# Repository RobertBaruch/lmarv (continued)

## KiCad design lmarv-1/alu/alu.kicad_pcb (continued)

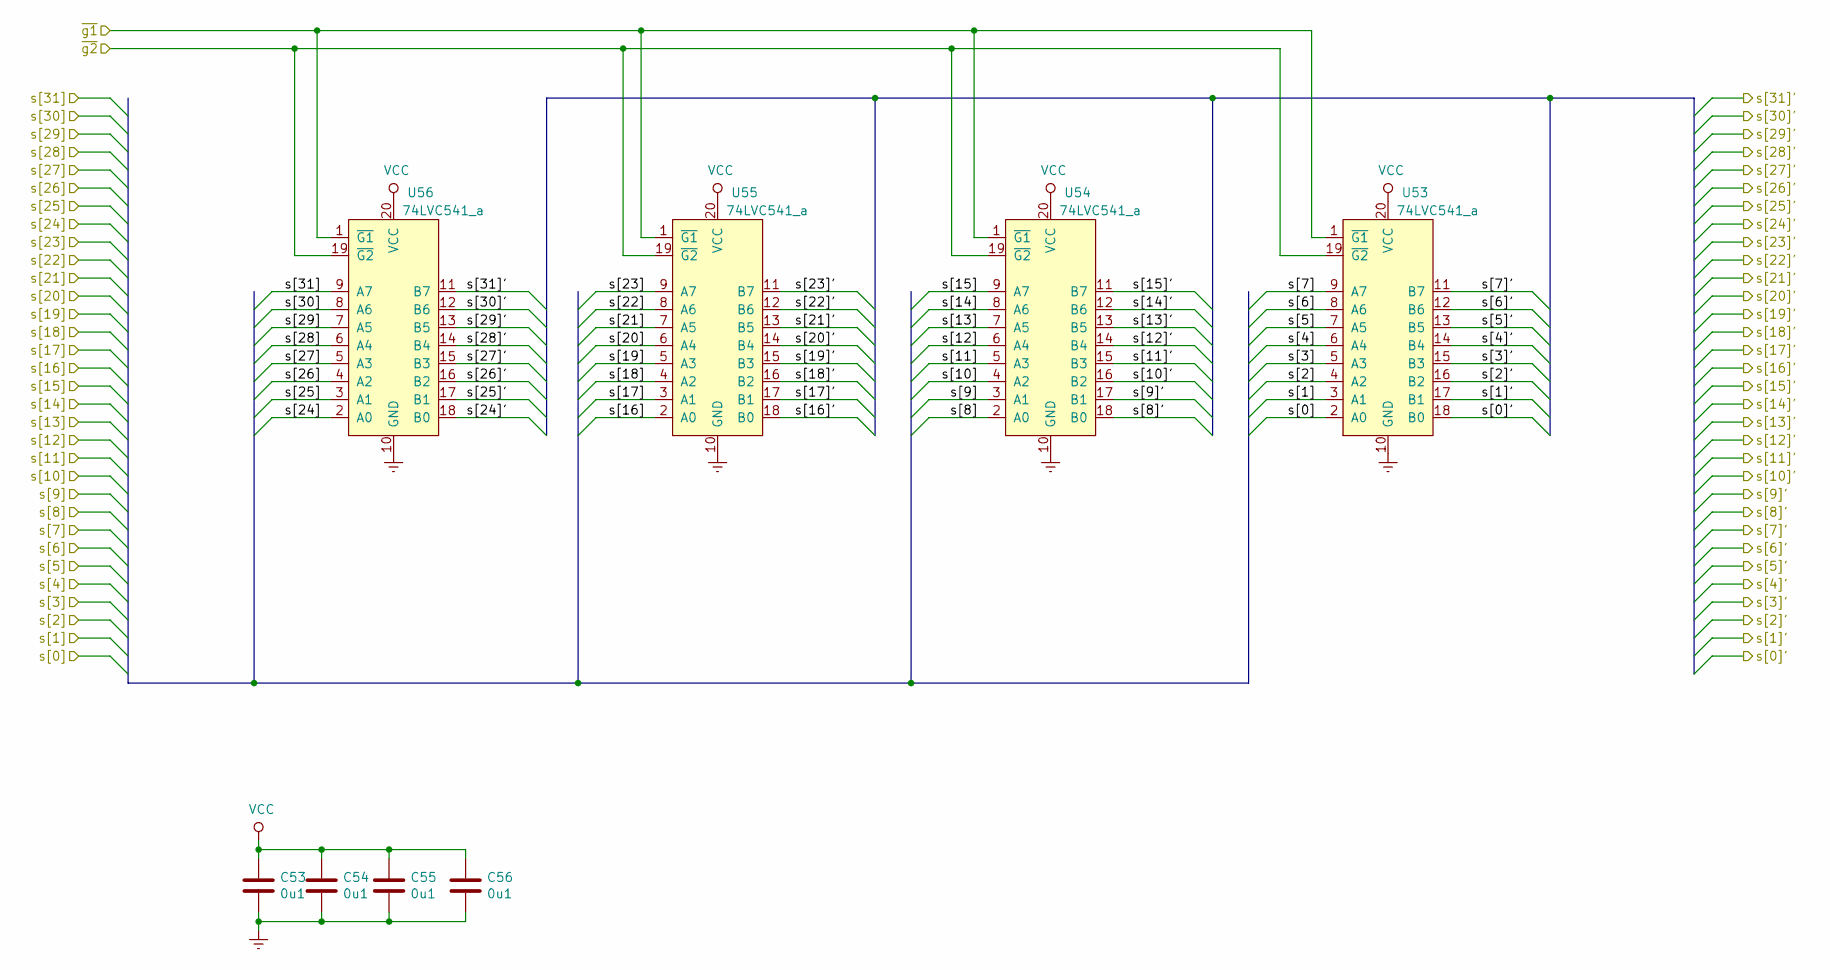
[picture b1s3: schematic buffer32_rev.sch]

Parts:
C13, C14, C15, C16: 0u1; C_0603_1608Metric
U53, U54, U55, U56: 74LVC541_a; TSSOP-20_4.4x6.5mm_P0.65mm

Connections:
/rd[0]: U53.18 (B0); also elsewhere on the board
/rd[1]: U53.17 (B1); also elsewhere on the board
/rd[2]: U53.16 (B2); also elsewhere on the board
/rd[3]: U53.15 (B3); also elsewhere on the board
/rd[4]: U53.14 (B4); also elsewhere on the board
/rd[5]: U53.13 (B5); also elsewhere on the board
/rd[6]: U53.12 (B6); also elsewhere on the board
/rd[7]: U53.11 (B7); also elsewhere on the board
/rd[8]: U54.18 (B0); also elsewhere on the board
/rd[9]: U54.17 (B1); also elsewhere on the board
/rd[10]: U54.16 (B2); also elsewhere on the board
/rd[11]: U54.15 (B3); also elsewhere on the board
/rd[12]: U54.14 (B4); also elsewhere on the board
/rd[13]: U54.13 (B5); also elsewhere on the board
/rd[14]: U54.12 (B6); also elsewhere on the board
/rd[15]: U54.11 (B7); also elsewhere on the board
/rd[16]: U55.18 (B0); also elsewhere on the board
/rd[17]: U55.17 (B1); also elsewhere on the board
/rd[18]: U55.16 (B2); also elsewhere on the board
/rd[19]: U55.15 (B3); also elsewhere on the board
/rd[20]: U55.14 (B4); also elsewhere on the board
/rd[21]: U55.13 (B5); also elsewhere on the board
/rd[22]: U55.12 (B6); also elsewhere on the board
/rd[23]: U55.11 (B7); also elsewhere on the board
/rd[24]: U56.18 (B0); also elsewhere on the board
/rd[25]: U56.17 (B1); also elsewhere on the board
/rd[26]: U56.16 (B2); also elsewhere on the board
/rd[27]: U56.15 (B3); also elsewhere on the board
/rd[28]: U56.14 (B4); also elsewhere on the board
/rd[29]: U56.13 (B5); also elsewhere on the board
/rd[30]: U56.12 (B6); also elsewhere on the board
/rd[31]: U56.11 (B7); also elsewhere on the board
/rdb[0]': U53.2 (A0); also elsewhere on the board
/rdb[1]: U53.3 (A1); also elsewhere on the board
/rdb[2]: U53.4 (A2); also elsewhere on the board
/rdb[3]: U53.5 (A3); also elsewhere on the board
/rdb[4]: U53.6 (A4); also elsewhere on the board
/rdb[5]: U53.7 (A5); also elsewhere on the board
/rdb[6]: U53.8 (A6); also elsewhere on the board
/rdb[7]: U53.9 (A7); also elsewhere on the board
/rdb[8]: U54.2 (A0); also elsewhere on the board
/rdb[9]: U54.3 (A1); also elsewhere on the board
/rdb[10]: U54.4 (A2); also elsewhere on the board
/rdb[11]: U54.5 (A3); also elsewhere on the board
/rdb[12]: U54.6 (A4); also elsewhere on the board
/rdb[13]: U54.7 (A5); also elsewhere on the board
/rdb[14]: U54.8 (A6); also elsewhere on the board
/rdb[15]: U54.9 (A7); also elsewhere on the board
/rdb[16]: U55.2 (A0); also elsewhere on the board
/rdb[17]: U55.3 (A1); also elsewhere on the board
/rdb[18]: U55.4 (A2); also elsewhere on the board
/rdb[19]: U55.5 (A3); also elsewhere on the board
/rdb[20]: U55.6 (A4); also elsewhere on the board
/rdb[21]: U55.7 (A5); also elsewhere on the board
/rdb[22]: U55.8 (A6); also elsewhere on the board
/rdb[23]: U55.9 (A7); also elsewhere on the board
/rdb[24]: U56.2 (A0); also elsewhere on the board
/rdb[25]: U56.3 (A1); also elsewhere on the board
/rdb[26]: U56.4 (A2); also elsewhere on the board
/rdb[27]: U56.5 (A3); also elsewhere on the board
/rdb[28]: U56.6 (A4); also elsewhere on the board
/rdb[29]: U56.7 (A5); also elsewhere on the board
/rdb[30]: U56.8 (A6); also elsewhere on the board
/rdb[31]: U56.9 (A7); also elsewhere on the board
/~alu_oe: U53.1 (~G1), U53.19 (~G2), U54.1 (~G1), U54.19 (~G2), U55.1 (~G1), U55.19 (~G2), U56.1 (~G1), U56.19 (~G2); also elsewhere on the board

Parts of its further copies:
C6, C7, C8, C9, C10, C11, C12, C17, C18, C19, C20, C21, C22, C23, C53, C54, C55, C56, C60: 0u1; C_0603_1608Metric

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
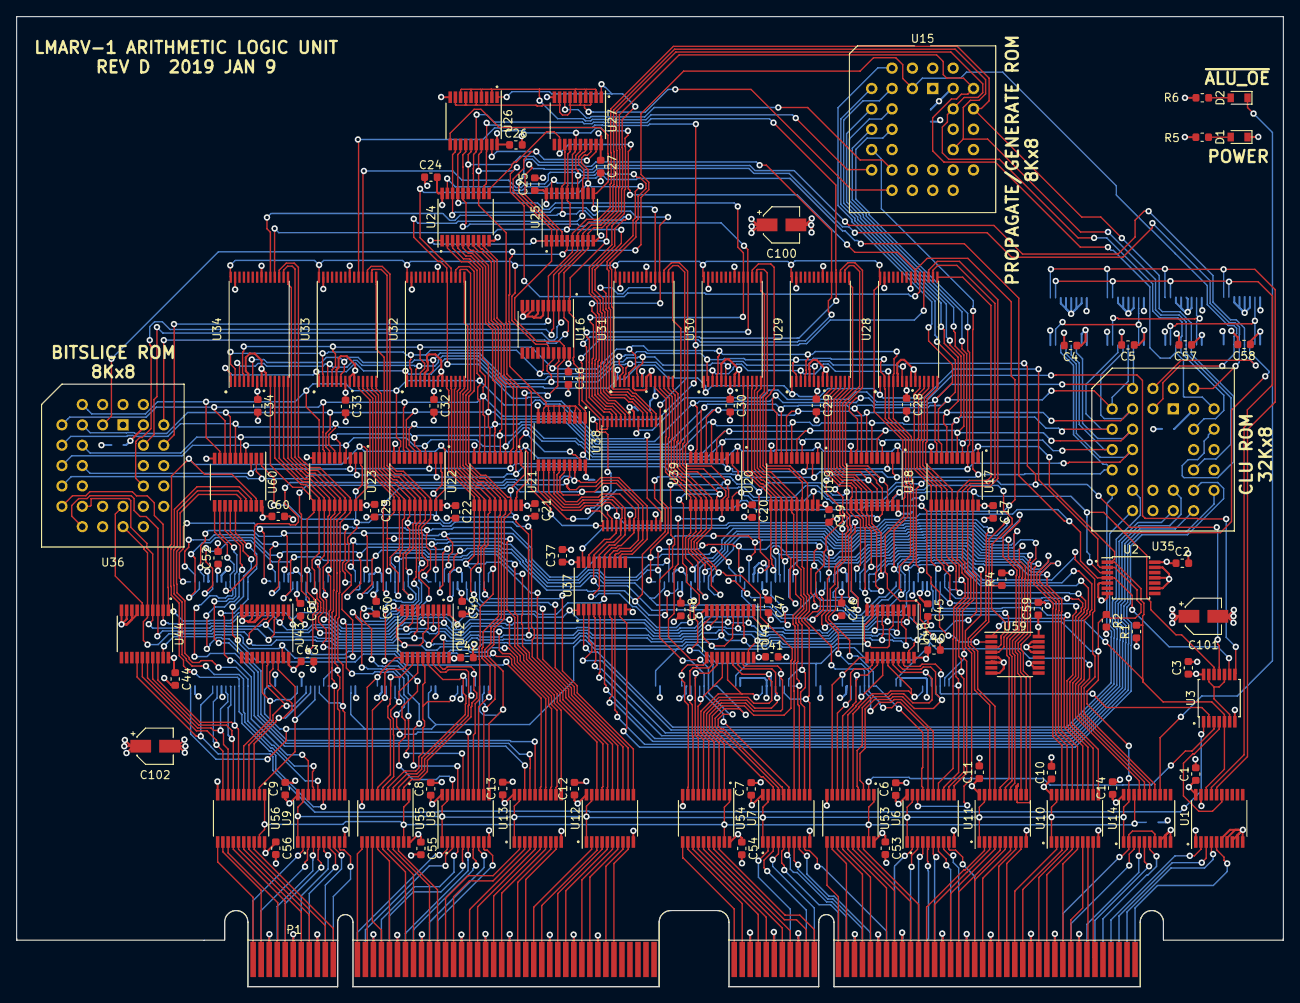
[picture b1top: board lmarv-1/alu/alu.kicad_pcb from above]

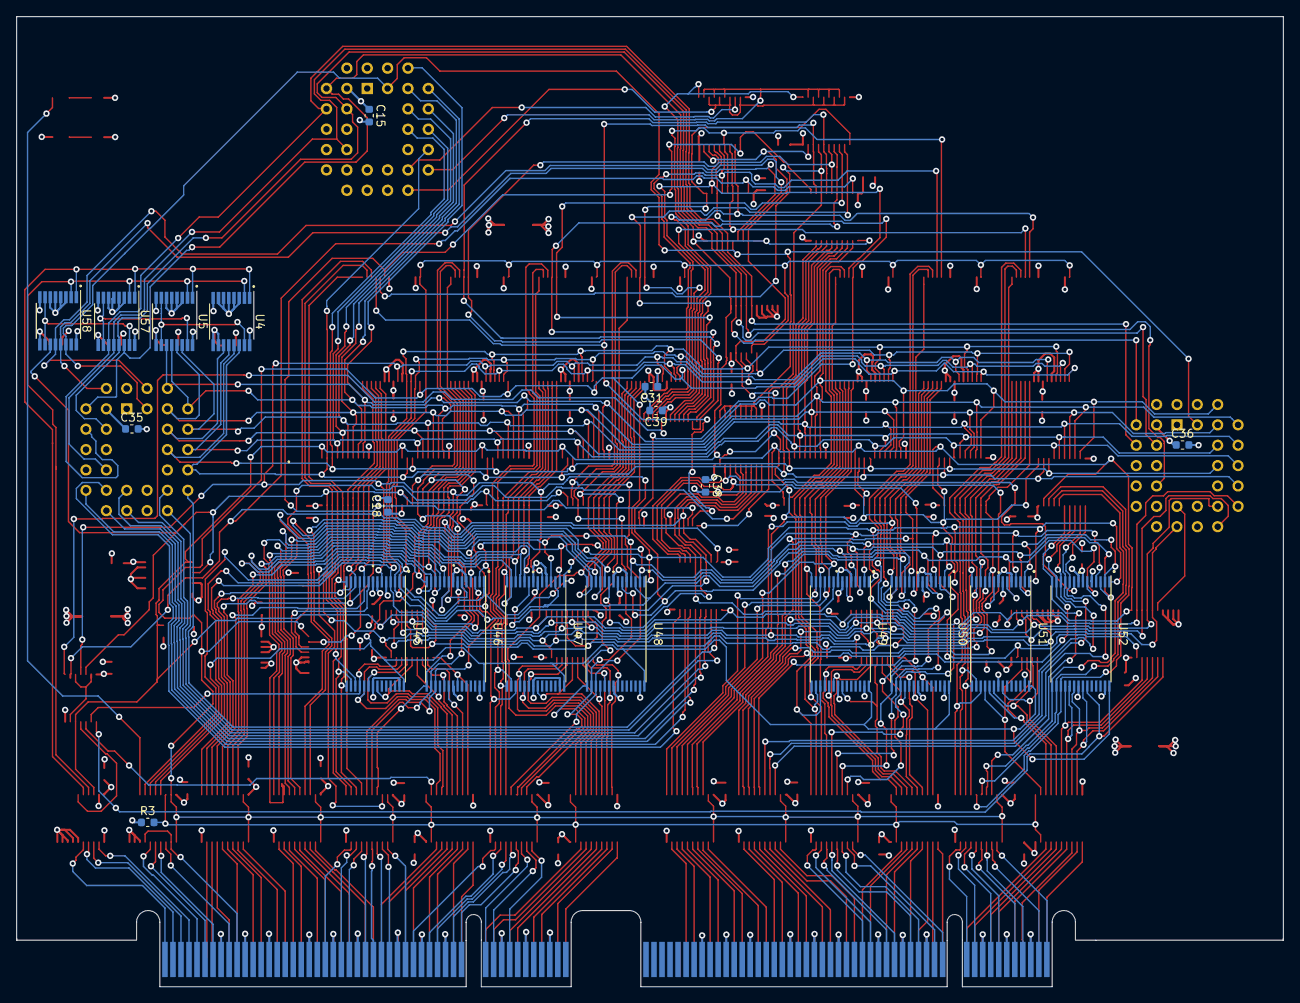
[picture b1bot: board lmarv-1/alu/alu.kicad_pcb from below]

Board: 4 copper layers, 158.0 x 121.0 mm, 132 parts (20 on the bottom side), 281 nets.

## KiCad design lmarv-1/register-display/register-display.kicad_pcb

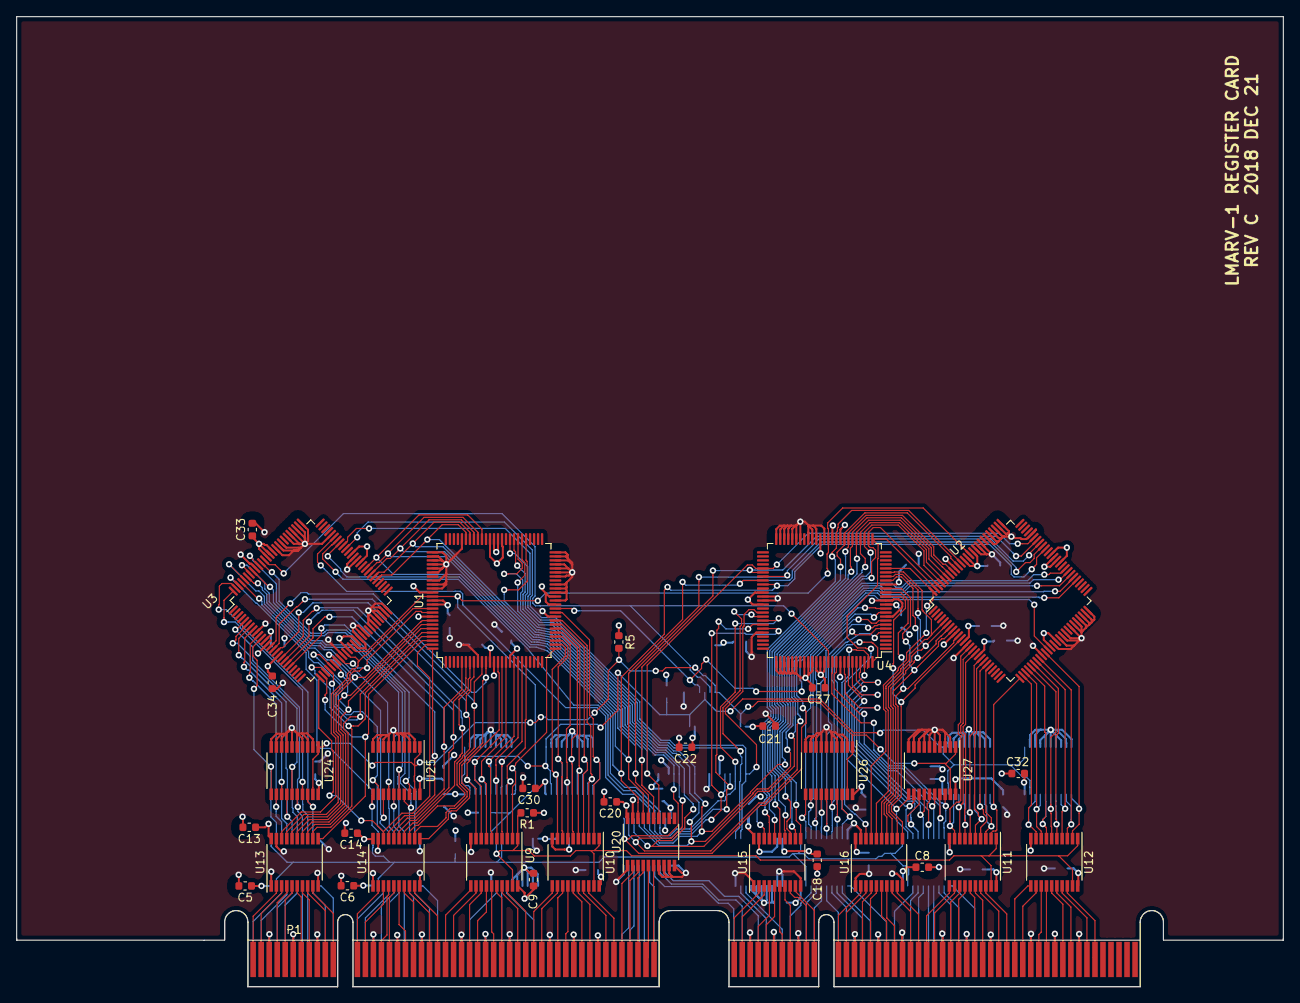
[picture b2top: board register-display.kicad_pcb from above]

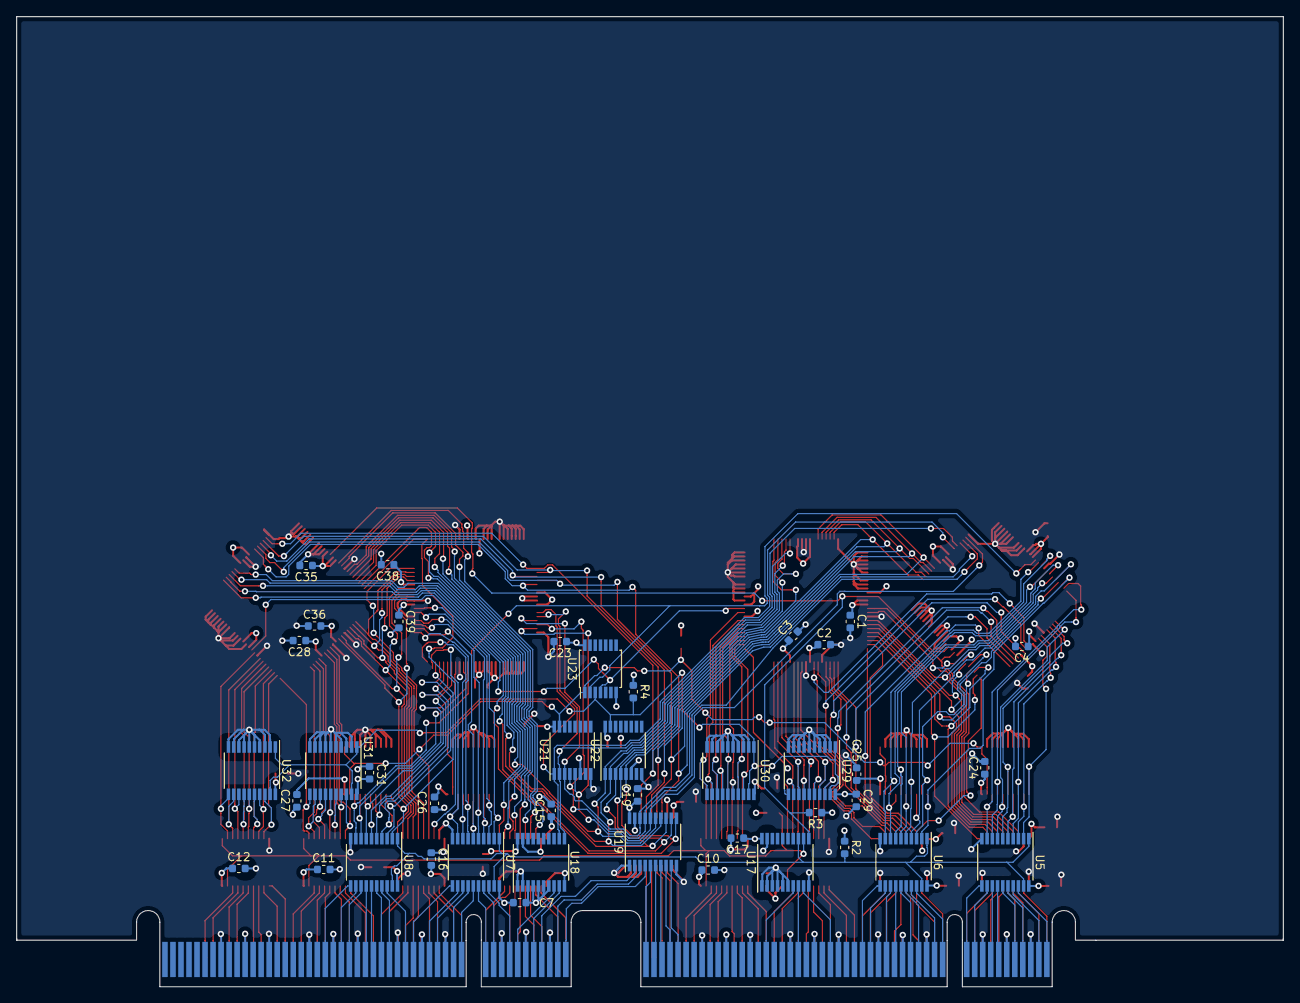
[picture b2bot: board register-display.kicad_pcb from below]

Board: 4 copper layers, 158.0 x 121.0 mm, 76 parts (41 on the bottom side), 234 nets.

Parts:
C1, C2, C3, C4, C5, C6, C7, C8, C9, C10, C11, C12, C13, C14, C15, C16, C17, C18, C19, C20, C21, C22, C23, C24, C25, C26, C27, C28, C29, C30, C31, C32, C33, C34, C35, C36, C37, C38, C39: 0u1; C_0603_1608Metric
P1: dual-pcie-cardedge_split; PCI-EXPRESS
R1, R2, R3, R4, R5: 47k; R_0603_1608Metric
U1, U2, U3, U4: IDT70V24_TQ100; TQFP-100_14x14mm_P0.5mm
U5, U6, U7, U8, U13, U14, U15, U16, U17, U18, U19, U20, U29, U30, U31, U32: 74LVC541; TSSOP-20_4.4x6.5mm_P0.65mm
U9, U10, U11, U12, U24, U25, U26, U27: 74LVC541_a; TSSOP-20_4.4x6.5mm_P0.65mm
U21, U22: 74LVC138; TSSOP-16_4.4x5mm_P0.65mm
U23: 74LVC04; TSSOP-14_4.4x5mm_P0.65mm

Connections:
/rd[0]: P1.71, U16.9
/rd[0]': U2.11, U4.14, U16.11
/rd[1]: P1.70, U16.8
/rd[1]': U2.10, U4.15, U16.12
/rd[2]: P1.68, U16.7
/rd[2]': U2.8, U4.16, U16.13
/rd[3]: P1.67, U16.6
/rd[3]': U2.7, U4.18, U16.14
/rd[4]: P1.65, U16.5
/rd[4]': U2.6, U4.19, U16.15
/rd[5]: P1.64, U16.4
/rd[5]': U2.5, U4.20, U16.16
/rd[6]: P1.62, U16.3
/rd[6]': U2.100, U4.21, U16.17
/rd[7]: P1.61, U16.2
/rd[7]': U2.99, U4.26, U16.18
/rd[8]: P1.60, U15.9
/rd[8]': U2.98, U4.27, U15.11
/rd[9]: P1.59, U15.8
/rd[9]': U2.97, U4.28, U15.12
/rd[10]: P1.57, U15.7
/rd[10]': U2.96, U4.29, U15.13
/rd[11]: P1.56, U15.6
/rd[11]': U2.95, U4.30, U15.14
/rd[12]: P1.54, U15.5
/rd[12]': U2.94, U4.31, U15.15
/rd[13]: P1.53, U15.4
/rd[13]': U2.93, U4.32, U15.16
/rd[14]: P1.51, U15.3
/rd[14]': U2.91, U4.33, U15.17
/rd[15]: P1.50, U15.2
/rd[15]': U2.90, U4.35, U15.18
/rd[16]: P1.22, U14.9
/rd[16]': U1.11, U3.14, U14.11
/rd[17]: P1.21, U14.8
/rd[17]': U1.10, U3.15, U14.12
/rd[18]: P1.19, U14.7
/rd[18]': U1.8, U3.16, U14.13
/rd[19]: P1.18, U14.6
/rd[19]': U1.7, U3.18, U14.14
/rd[20]: P1.16, U14.5
/rd[20]': U1.6, U3.19, U14.15
/rd[21]: P1.15, U14.4
/rd[21]': U1.5, U3.20, U14.16
/rd[22]: P1.13, U14.3
/rd[22]': U1.100, U3.21, U14.17
/rd[23]: P1.12, U14.2
/rd[23]': U1.99, U3.26, U14.18
/rd[24]: P1.11, U13.9
/rd[24]': U1.98, U3.27, U13.11
/rd[25]: P1.10, U13.8
/rd[25]': U1.97, U3.28, U13.12
/rd[26]: P1.8, U13.7
/rd[26]': U1.96, U3.29, U13.13
/rd[27]: P1.7, U13.6
/rd[27]': U1.95, U3.30, U13.14
/rd[28]: P1.5, U13.5
/rd[28]': U1.94, U3.31, U13.15
/rd[29]: P1.4, U13.4
/rd[29]': U1.93, U3.32, U13.16
/rd[30]: P1.2, U13.3
/rd[30]': U1.91, U3.33, U13.17
/rd[31]: P1.1, U13.2
/rd[31]': U1.90, U3.35, U13.18
/rda[0]: P1.45, U20.2
/rda[0]': U1.66, U2.66, U3.59, U4.59, U20.18
/rda[1]: P1.46, U20.3
/rda[1]': U1.67, U2.67, U3.58, U4.58, U20.17
/rda[2]: P1.47, U20.4
/rda[2]': U1.68, U2.68, U3.57, U4.57, U20.16
/rda[3]: P1.48, U20.5
/rda[3]': U1.69, U2.69, U3.56, U4.56, U20.15
/rda[4]: P1.49, U20.6
/rda[4]': U1.70, U2.70, U3.55, U4.55, U20.14
/rs1[0]: P1.176, U8.11
/rs1[0]': U4.90, U8.9, U27.18
/rs1[1]: P1.174, U8.12
/rs1[1]': U4.91, U8.8, U27.17
/rs1[2]: P1.173, U8.13
/rs1[2]': U4.93, U8.7, U27.16
/rs1[3]: P1.171, U8.14
/rs1[3]': U4.94, U8.6, U27.15
/rs1[4]: P1.170, U8.15
/rs1[4]': U4.95, U8.5, U27.14
/rs1[5]: P1.169, U8.16
/rs1[5]': U4.96, U8.4, U27.13
/rs1[6]: P1.168, U8.17
/rs1[6]': U4.97, U8.3, U27.12
/rs1[7]: P1.166, U8.18
/rs1[7]': U4.98, U8.2, U27.11
/rs1[8]: P1.165, U7.11
/rs1[8]': U4.99, U7.9, U26.18
/rs1[9]: P1.163, U7.12
/rs1[9]': U4.100, U7.8, U26.17
/rs1[10]: P1.162, U7.13
/rs1[10]': U4.5, U7.7, U26.16
/rs1[11]: P1.160, U7.14
/rs1[11]': U4.6, U7.6, U26.15
/rs1[12]: P1.159, U7.15
/rs1[12]': U4.7, U7.5, U26.14
/rs1[13]: P1.158, U7.16
/rs1[13]': U4.8, U7.4, U26.13
/rs1[14]: P1.157, U7.17
/rs1[14]': U4.10, U7.3, U26.12
/rs1[15]: P1.155, U7.18
/rs1[15]': U4.11, U7.2, U26.11
/rs1[16]: P1.120, U6.11
/rs1[16]': U3.90, U6.9, U25.18
/rs1[17]: P1.119, U6.12
/rs1[17]': U3.91, U6.8, U25.17
/rs1[18]: P1.117, U6.13
/rs1[18]': U3.93, U6.7, U25.16
/rs1[19]: P1.116, U6.14
/rs1[19]': U3.94, U6.6, U25.15
/rs1[20]: P1.114, U6.15
/rs1[20]': U3.95, U6.5, U25.14
/rs1[21]: P1.113, U6.16
/rs1[21]': U3.96, U6.4, U25.13
/rs1[22]: P1.111, U6.17
/rs1[22]': U3.97, U6.3, U25.12
/rs1[23]: P1.110, U6.18
/rs1[23]': U3.98, U6.2, U25.11
/rs1[24]: P1.109, U5.11
/rs1[24]': U3.99, U5.9, U24.18
/rs1[25]: P1.108, U5.12
/rs1[25]': U3.100, U5.8, U24.17
/rs1[26]: P1.106, U5.13
/rs1[26]': U3.5, U5.7, U24.16
/rs1[27]: P1.105, U5.14
/rs1[27]': U3.6, U5.6, U24.15
/rs1[28]: P1.103, U5.15
/rs1[28]': U3.7, U5.5, U24.14
/rs1[29]: P1.102, U5.16
/rs1[29]': U3.8, U5.4, U24.13
/rs1[30]: P1.100, U5.17
/rs1[30]': U3.10, U5.3, U24.12
/rs1[31]: P1.99, U5.18
/rs1[31]': U3.11, U5.2, U24.11
/rs1_zero: U3.89, U4.89, U23.2
/rs1a[0]: P1.154, U18.8
/rs1a[0]': U3.66, U4.66, U18.12, U21.1
/rs1a[1]: P1.152, U18.9
/rs1a[1]': U3.67, U4.67, U18.11, U21.2
/rs1a[2]: P1.151, U19.2
/rs1a[2]': U3.68, U4.68, U19.18, U21.3
/rs1a[3]: P1.149, U19.3
/rs1a[3]': U3.69, U4.69, U19.17, U21.4
/rs1a[4]: P1.148, U19.4
/rs1a[4]': U3.70, U4.70, U19.16, U21.5
/rs2[0]: P1.93, U12.18
/rs2[0]': U2.35, U12.2, U32.11
/rs2[1]: P1.92, U12.17
/rs2[1]': U2.33, U12.3, U32.12
/rs2[2]: P1.90, U12.16
/rs2[2]': U2.32, U12.4, U32.13
/rs2[3]: P1.89, U12.15
/rs2[3]': U2.31, U12.5, U32.14
/rs2[4]: P1.87, U12.14
/rs2[4]': U2.30, U12.6, U32.15
/rs2[5]: P1.86, U12.13
/rs2[5]': U2.29, U12.7, U32.16
/rs2[6]: P1.84, U12.12
/rs2[6]': U2.28, U12.8, U32.17
/rs2[7]: P1.83, U12.11
/rs2[7]': U2.27, U12.9, U32.18
/rs2[8]: P1.82, U11.18
/rs2[8]': U2.26, U11.2, U31.11
/rs2[9]: P1.81, U11.17
/rs2[9]': U2.21, U11.3, U31.12
/rs2[10]: P1.79, U11.16
/rs2[10]': U2.20, U11.4, U31.13
/rs2[11]: P1.78, U11.15
/rs2[11]': U2.19, U11.5, U31.14
/rs2[12]: P1.76, U11.14
/rs2[12]': U2.18, U11.6, U31.15
/rs2[13]: P1.75, U11.13
/rs2[13]': U2.16, U11.7, U31.16
/rs2[14]: P1.73, U11.12
/rs2[14]': U2.15, U11.8, U31.17
/rs2[15]: P1.72, U11.11
/rs2[15]': U2.14, U11.9, U31.18
/rs2[16]: P1.44, U10.18
/rs2[16]': U1.35, U10.2, U30.11
/rs2[17]: P1.43, U10.17
/rs2[17]': U1.33, U10.3, U30.12
/rs2[18]: P1.41, U10.16
/rs2[18]': U1.32, U10.4, U30.13
/rs2[19]: P1.40, U10.15
/rs2[19]': U1.31, U10.5, U30.14
/rs2[20]: P1.38, U10.14
/rs2[20]': U1.30, U10.6, U30.15
/rs2[21]: P1.37, U10.13
/rs2[21]': U1.29, U10.7, U30.16
/rs2[22]: P1.35, U10.12
/rs2[22]': U1.28, U10.8, U30.17
/rs2[23]: P1.34, U10.11
/rs2[23]': U1.27, U10.9, U30.18
/rs2[24]: P1.33, U9.18
/rs2[24]': U1.26, U9.2, U29.11
/rs2[25]: P1.32, U9.17
/rs2[25]': U1.21, U9.3, U29.12
/rs2[26]: P1.30, U9.16
/rs2[26]': U1.20, U9.4, U29.13
/rs2[27]: P1.29, U9.15
/rs2[27]': U1.19, U9.5, U29.14
/rs2[28]: P1.27, U9.14
/rs2[28]': U1.18, U9.6, U29.15
/rs2[29]: P1.26, U9.13
/rs2[29]': U1.16, U9.7, U29.16
/rs2[30]: P1.24, U9.12
/rs2[30]': U1.15, U9.8, U29.17
/rs2[31]: P1.23, U9.11
/rs2[31]': U1.14, U9.9, U29.18
/rs2_zero: U1.36, U2.36, U23.4
/rs2a[0]: P1.147, U19.5
/rs2a[0]': U1.59, U2.59, U19.15, U22.1
/rs2a[1]: P1.146, U19.6
/rs2a[1]': U1.58, U2.58, U19.14, U22.2
/rs2a[2]: P1.145, U19.7
/rs2a[2]': U1.57, U2.57, U19.13, U22.3
/rs2a[3]: P1.144, U19.8
/rs2a[3]': U1.56, U2.56, U19.12, U22.4
/rs2a[4]: P1.143, U19.9
/rs2a[4]': U1.55, U2.55, U19.11, U22.5
/~rd_wr: P1.124, U17.9
/~rd_wr~': R3.2, U1.87, U2.87, U3.37, U4.37, U17.11
/~rs1_rd: P1.132, U17.7
/~rs1_rd~': R2.2, U5.1, U5.19, U6.1, U6.19, U7.1, U7.19, U8.1, U8.19, U17.13
/~rs1_zero: R5.2, U21.15, U23.1, U24.1, U24.19, U25.1, U25.19, U26.1, U26.19, U27.1, U27.19
/~rs2_rd: P1.128, U17.8
/~rs2_rd~': R1.2, U9.1, U9.19, U10.1, U10.19, U11.1, U11.19, U12.1, U12.19, U17.12
/~rs2_zero: R4.2, U22.15, U23.3, U29.1, U29.19, U30.1, U30.19, U31.1, U31.19, U32.1, U32.19
GND: C1.2, C2.2, C3.2, C4.2, C5.2, C6.2, C7.2, C8.2, C9.2, C10.2, C11.2, C12.2, C13.2, C14.2, C15.2, C16.2, C17.2, C18.2, C19.2, C20.2, C21.2, C22.2, C23.2, C24.2, C25.2, C26.2, C27.2, C28.2, C29.2, C30.2, C31.2, C32.2, C33.2, C34.2, C35.2, C36.2, C37.2, C38.2, C39.2, P1.3, P1.9, P1.14, P1.20, P1.25, P1.31, P1.36, P1.42, P1.52, P1.58, P1.63, P1.69, P1.74, P1.80, P1.85, P1.91, P1.101, P1.107, P1.112, P1.118, P1.123, P1.129, P1.134, P1.140, P1.150, P1.156, P1.161, P1.167, P1.172, P1.178, P1.183, P1.189, U1.9, U1.13, U1.34, U1.38, U1.40, U1.41, U1.42, U1.44, U1.45, U1.46, U1.47, U1.48, U1.49, U1.50, U1.62, U1.63, U1.71, U1.76, U1.77, U1.78, U1.79, U1.80, U1.81, U1.83, U1.84, U1.85, U1.92, U2.9, U2.13, U2.34, U2.38, U2.40, U2.41, U2.42, U2.44, U2.45, U2.46, U2.47, U2.48, U2.49, U2.50, U2.62, U2.63, U2.71, U2.76, U2.77, U2.78, U2.79, U2.80, U2.81, U2.83, U2.84, U2.85, U2.92, U3.9, U3.13, U3.34, U3.38, U3.40, U3.41, U3.42, U3.44, U3.45, U3.46, U3.47, U3.48, U3.49, U3.50, U3.62, U3.63, U3.71, U3.76, U3.77, U3.78, U3.79, U3.80, U3.81, U3.83, U3.84, U3.85, U3.92, U4.9, U4.13, U4.34, U4.38, U4.40, U4.41, U4.42, U4.44, U4.45, U4.46, U4.47, U4.48, U4.49, U4.50, U4.62, U4.63, U4.71, U4.76, U4.77, U4.78, U4.79, U4.80, U4.81, U4.83, U4.84, U4.85, U4.92, U5.10, U6.10, U7.10, U8.10, U9.10, U10.10, U11.10, U12.10, U13.1, U13.10, U13.19, U14.1, U14.10, U14.19, U15.1, U15.10, U15.19, U16.1, U16.10, U16.19, U17.1, U17.2, U17.3, U17.4, U17.5, U17.6, U17.10, U17.19, U18.1, U18.2, U18.3, U18.4, U18.5, U18.6, U18.7, U18.10, U18.19, U19.1, U19.10, U19.19, U20.1, U20.7, U20.8, U20.9, U20.10, U20.19, U21.8, U22.8, U23.7, U24.2, U24.3, U24.4, U24.5, U24.6, U24.7, U24.8, U24.9, U24.10, U25.2, U25.3, U25.4, U25.5, U25.6, U25.7, U25.8, U25.9, U25.10, U26.2, U26.3, U26.4, U26.5, U26.6, U26.7, U26.8, U26.9, U26.10, U27.2, U27.3, U27.4, U27.5, U27.6, U27.7, U27.8, U27.9, U27.10, U29.2, U29.3, U29.4, U29.5, U29.6, U29.7, U29.8, U29.9, U29.10, U30.2, U30.3, U30.4, U30.5, U30.6, U30.7, U30.8, U30.9, U30.10, U31.2, U31.3, U31.4, U31.5, U31.6, U31.7, U31.8, U31.9, U31.10, U32.2, U32.3, U32.4, U32.5, U32.6, U32.7, U32.8, U32.9, U32.10
VCC: C1.1, C2.1, C3.1, C4.1, C5.1, C6.1, C7.1, C8.1, C9.1, C10.1, C11.1, C12.1, C13.1, C14.1, C15.1, C16.1, C17.1, C18.1, C19.1, C20.1, C21.1, C22.1, C23.1, C24.1, C25.1, C26.1, C27.1, C28.1, C29.1, C30.1, C31.1, C32.1, C33.1, C34.1, C35.1, C36.1, C37.1, C38.1, C39.1, P1.6, P1.17, P1.28, P1.39, P1.55, P1.66, P1.77, P1.88, P1.104, P1.115, P1.126, P1.137, P1.153, P1.164, P1.175, P1.186, R1.1, R2.1, R3.1, R4.1, R5.1, U1.12, U1.17, U1.37, U1.39, U1.61, U1.64, U1.86, U1.88, U1.89, U2.12, U2.17, U2.37, U2.39, U2.61, U2.64, U2.86, U2.88, U2.89, U3.12, U3.17, U3.36, U3.39, U3.61, U3.64, U3.86, U3.87, U3.88, U4.12, U4.17, U4.36, U4.39, U4.61, U4.64, U4.86, U4.87, U4.88, U5.20, U6.20, U7.20, U8.20, U9.20, U10.20, U11.20, U12.20, U13.20, U14.20, U15.20, U16.20, U17.20, U18.20, U19.20, U20.20, U21.6, U21.16, U22.6, U22.16, U23.14, U24.20, U25.20, U26.20, U27.20, U29.20, U30.20, U31.20, U32.20

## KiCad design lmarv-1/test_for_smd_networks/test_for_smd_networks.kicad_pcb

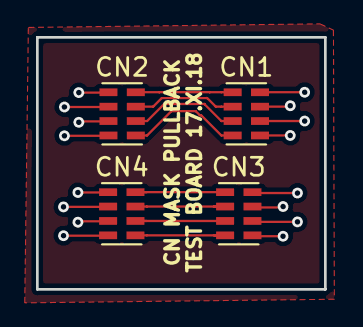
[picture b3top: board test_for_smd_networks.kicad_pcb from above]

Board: 2 copper layers, 16.0 x 14.0 mm, 4 parts (0 on the bottom side), 9 nets.

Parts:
CN1, CN2, CN3, CN4: CKCA43C0G1H; RN_1206_4

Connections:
GND: CN1.5, CN1.6, CN1.7, CN1.8, CN2.1, CN2.2, CN2.3, CN2.4, CN3.5, CN3.6, CN3.7, CN3.8, CN4.1, CN4.2, CN4.3, CN4.4
unnamed: CN1.1, CN2.8
unnamed: CN1.2, CN2.7
unnamed: CN1.3, CN2.6
unnamed: CN1.4, CN2.5
unnamed: CN3.1, CN4.8
unnamed: CN3.2, CN4.7
unnamed: CN3.3, CN4.6
unnamed: CN3.4, CN4.5
